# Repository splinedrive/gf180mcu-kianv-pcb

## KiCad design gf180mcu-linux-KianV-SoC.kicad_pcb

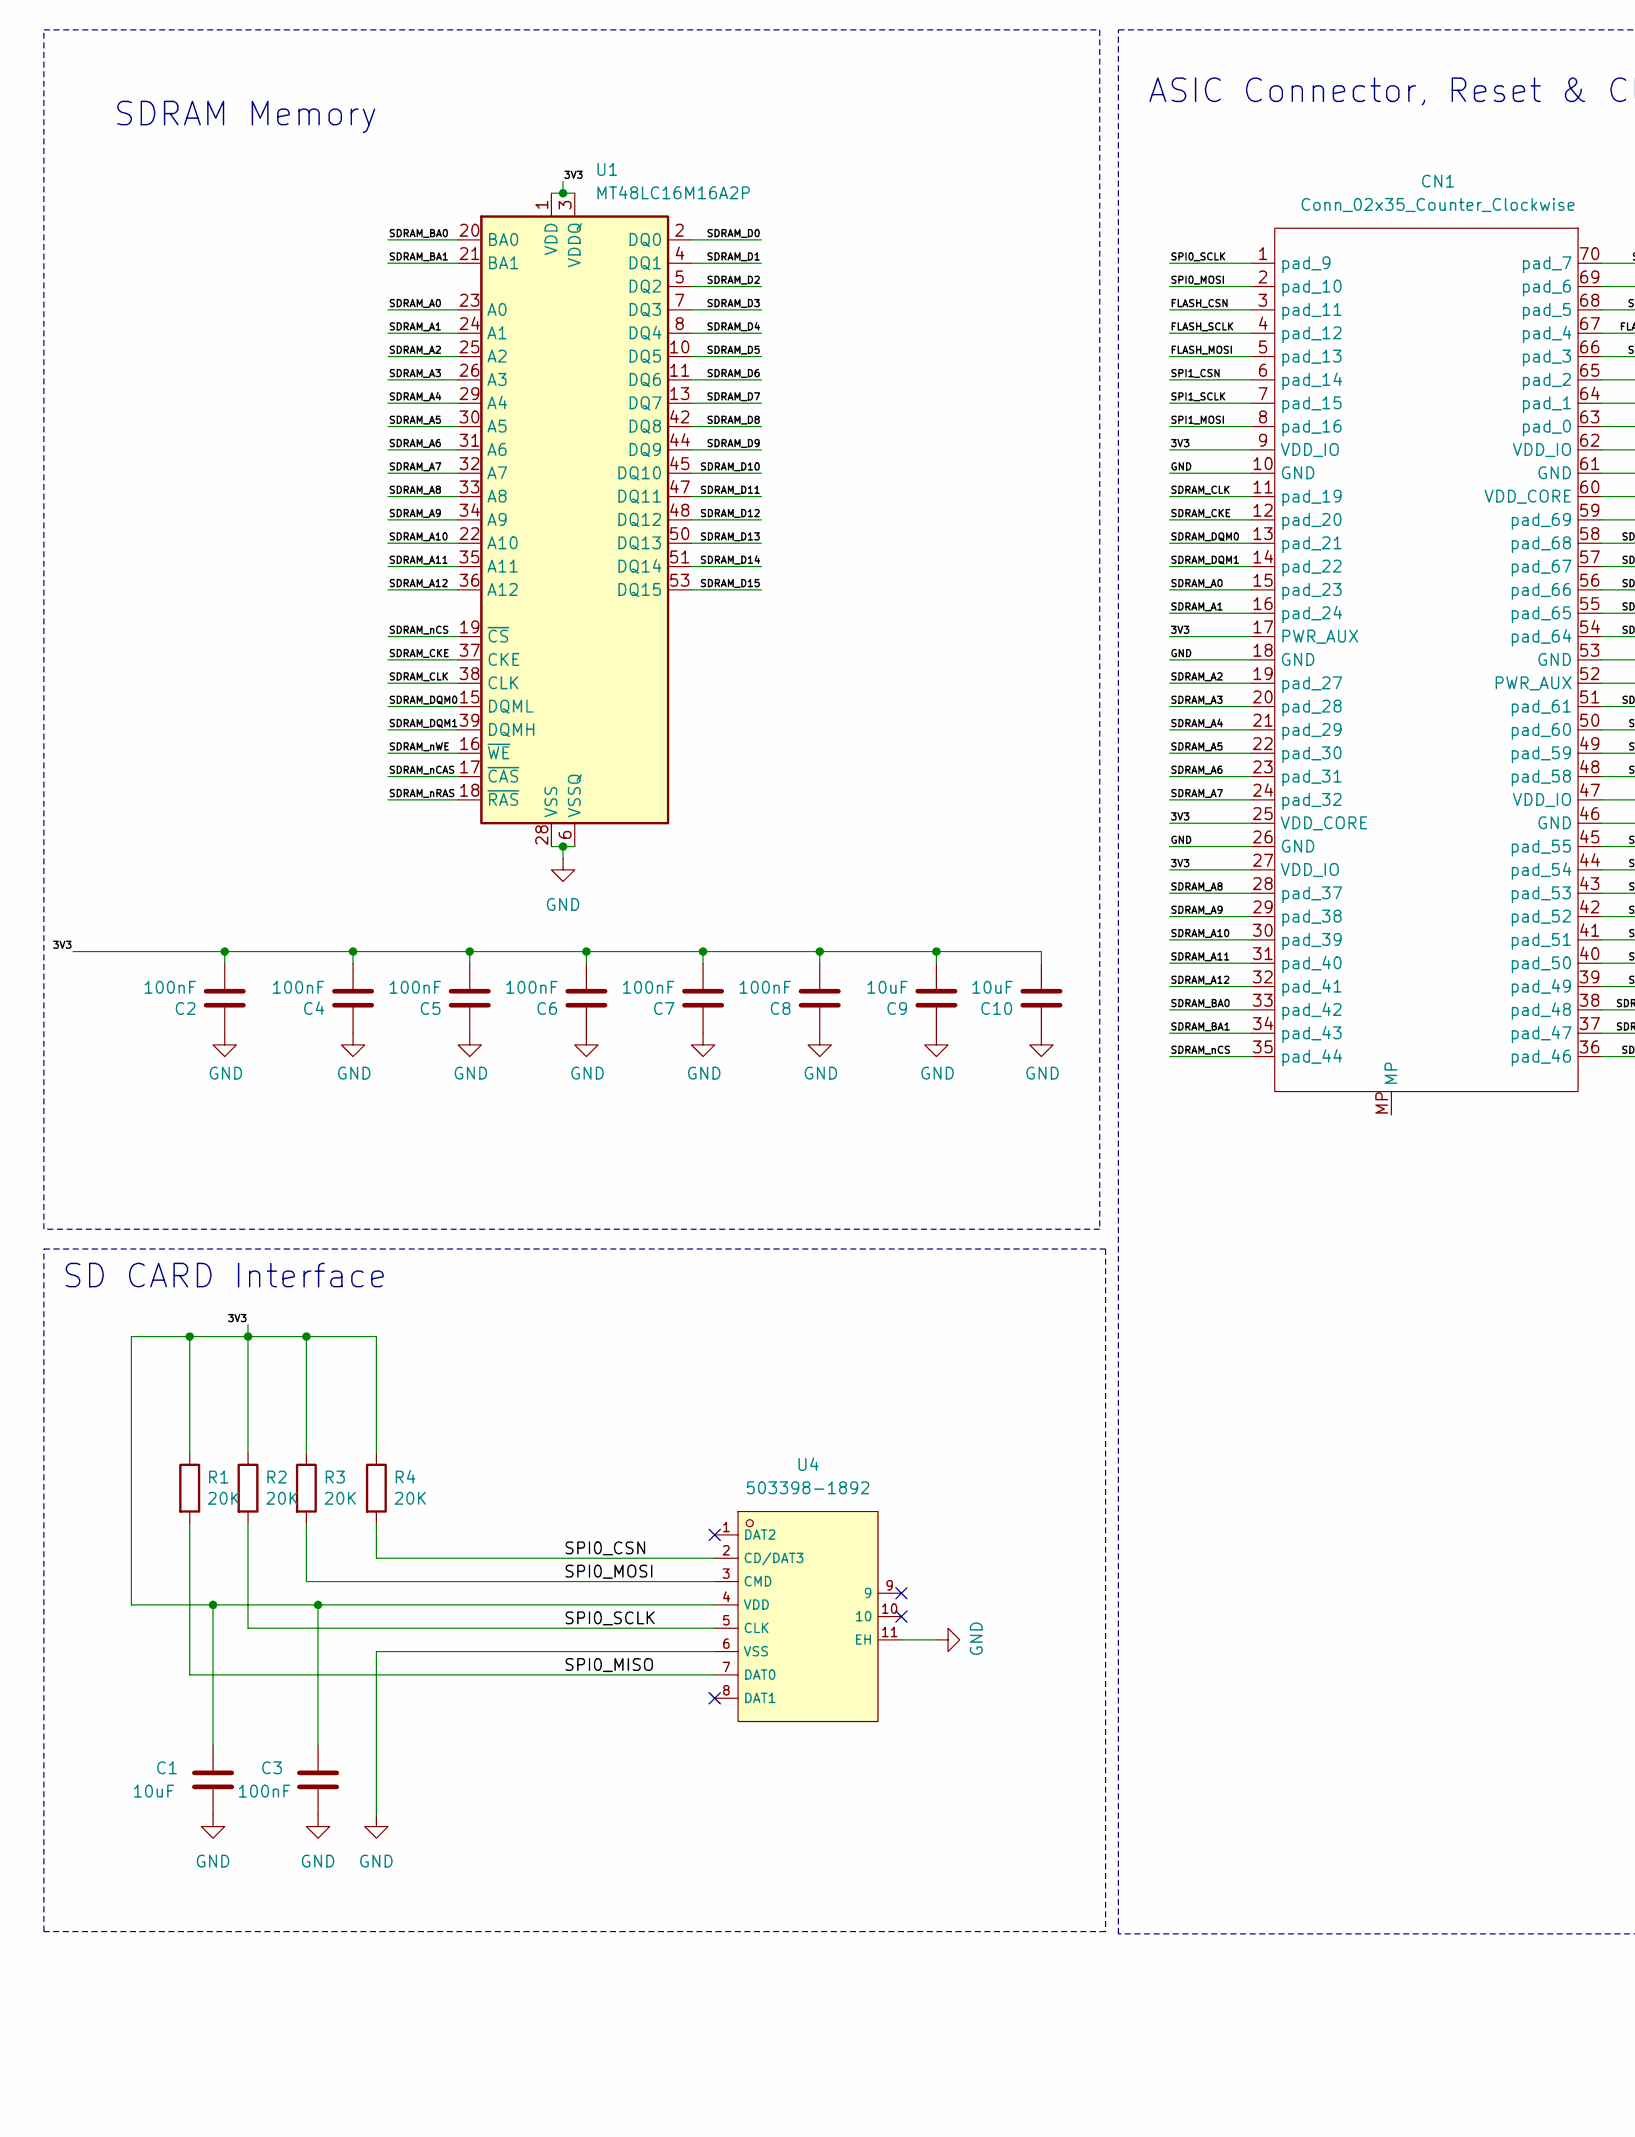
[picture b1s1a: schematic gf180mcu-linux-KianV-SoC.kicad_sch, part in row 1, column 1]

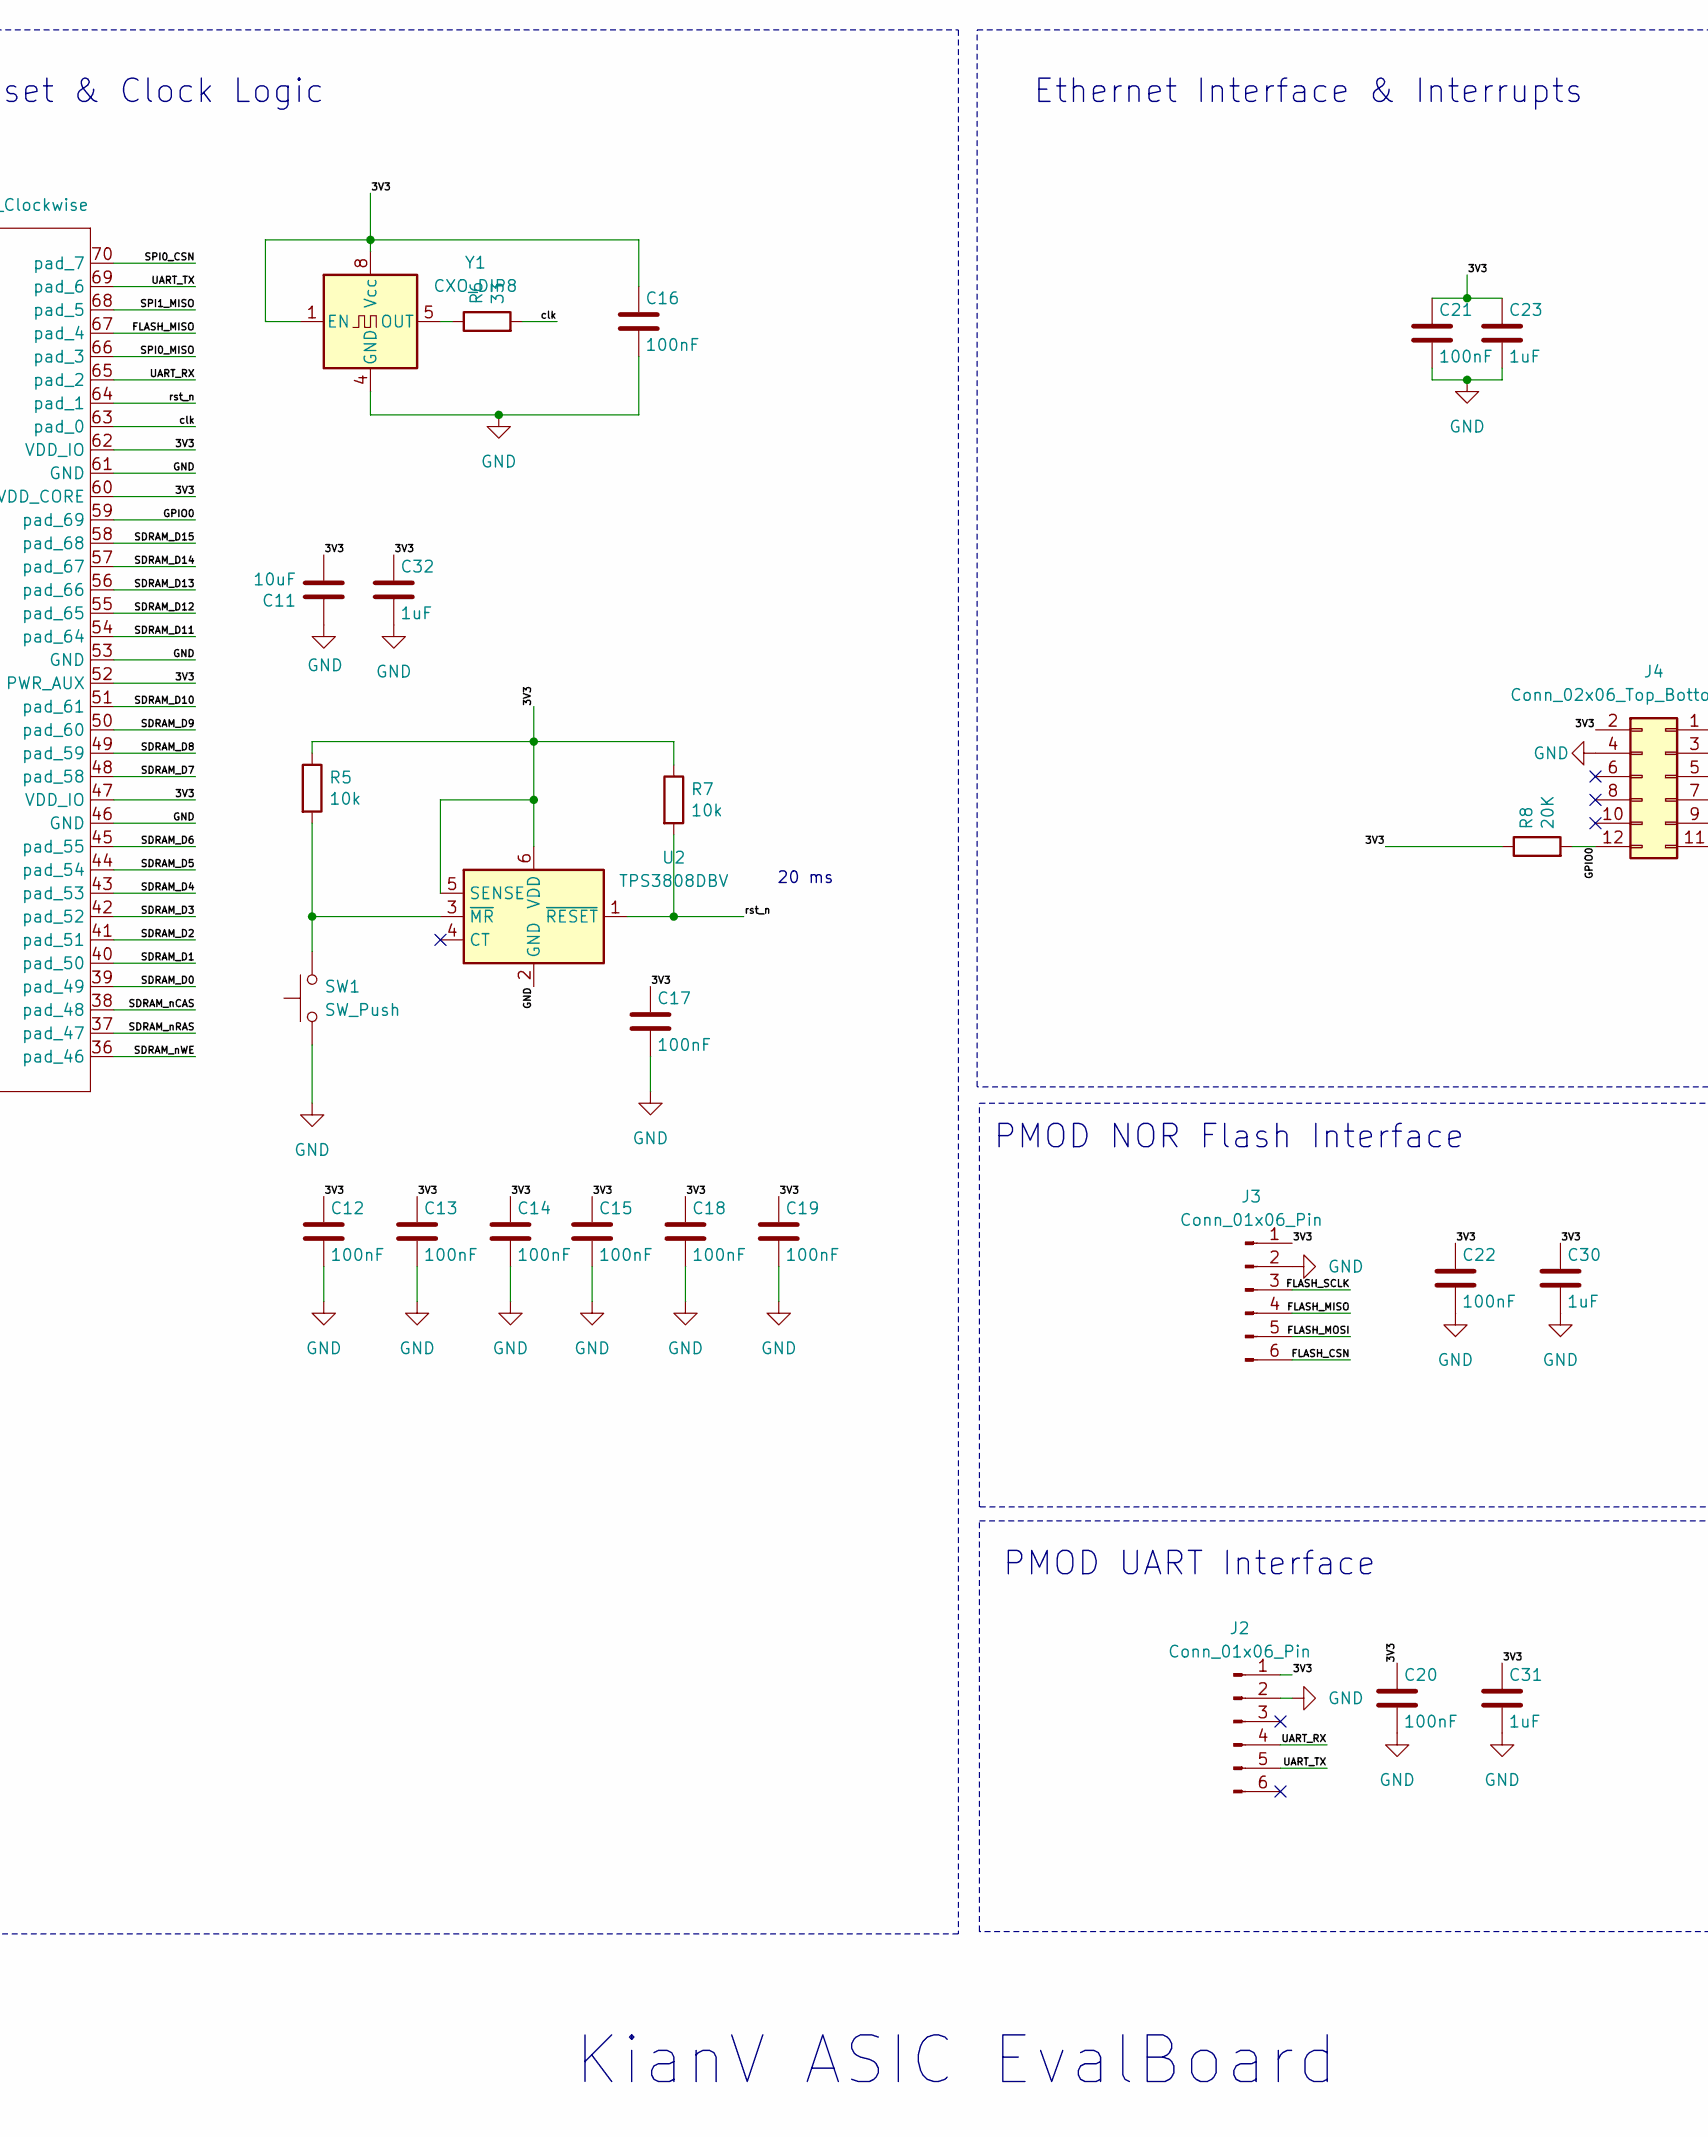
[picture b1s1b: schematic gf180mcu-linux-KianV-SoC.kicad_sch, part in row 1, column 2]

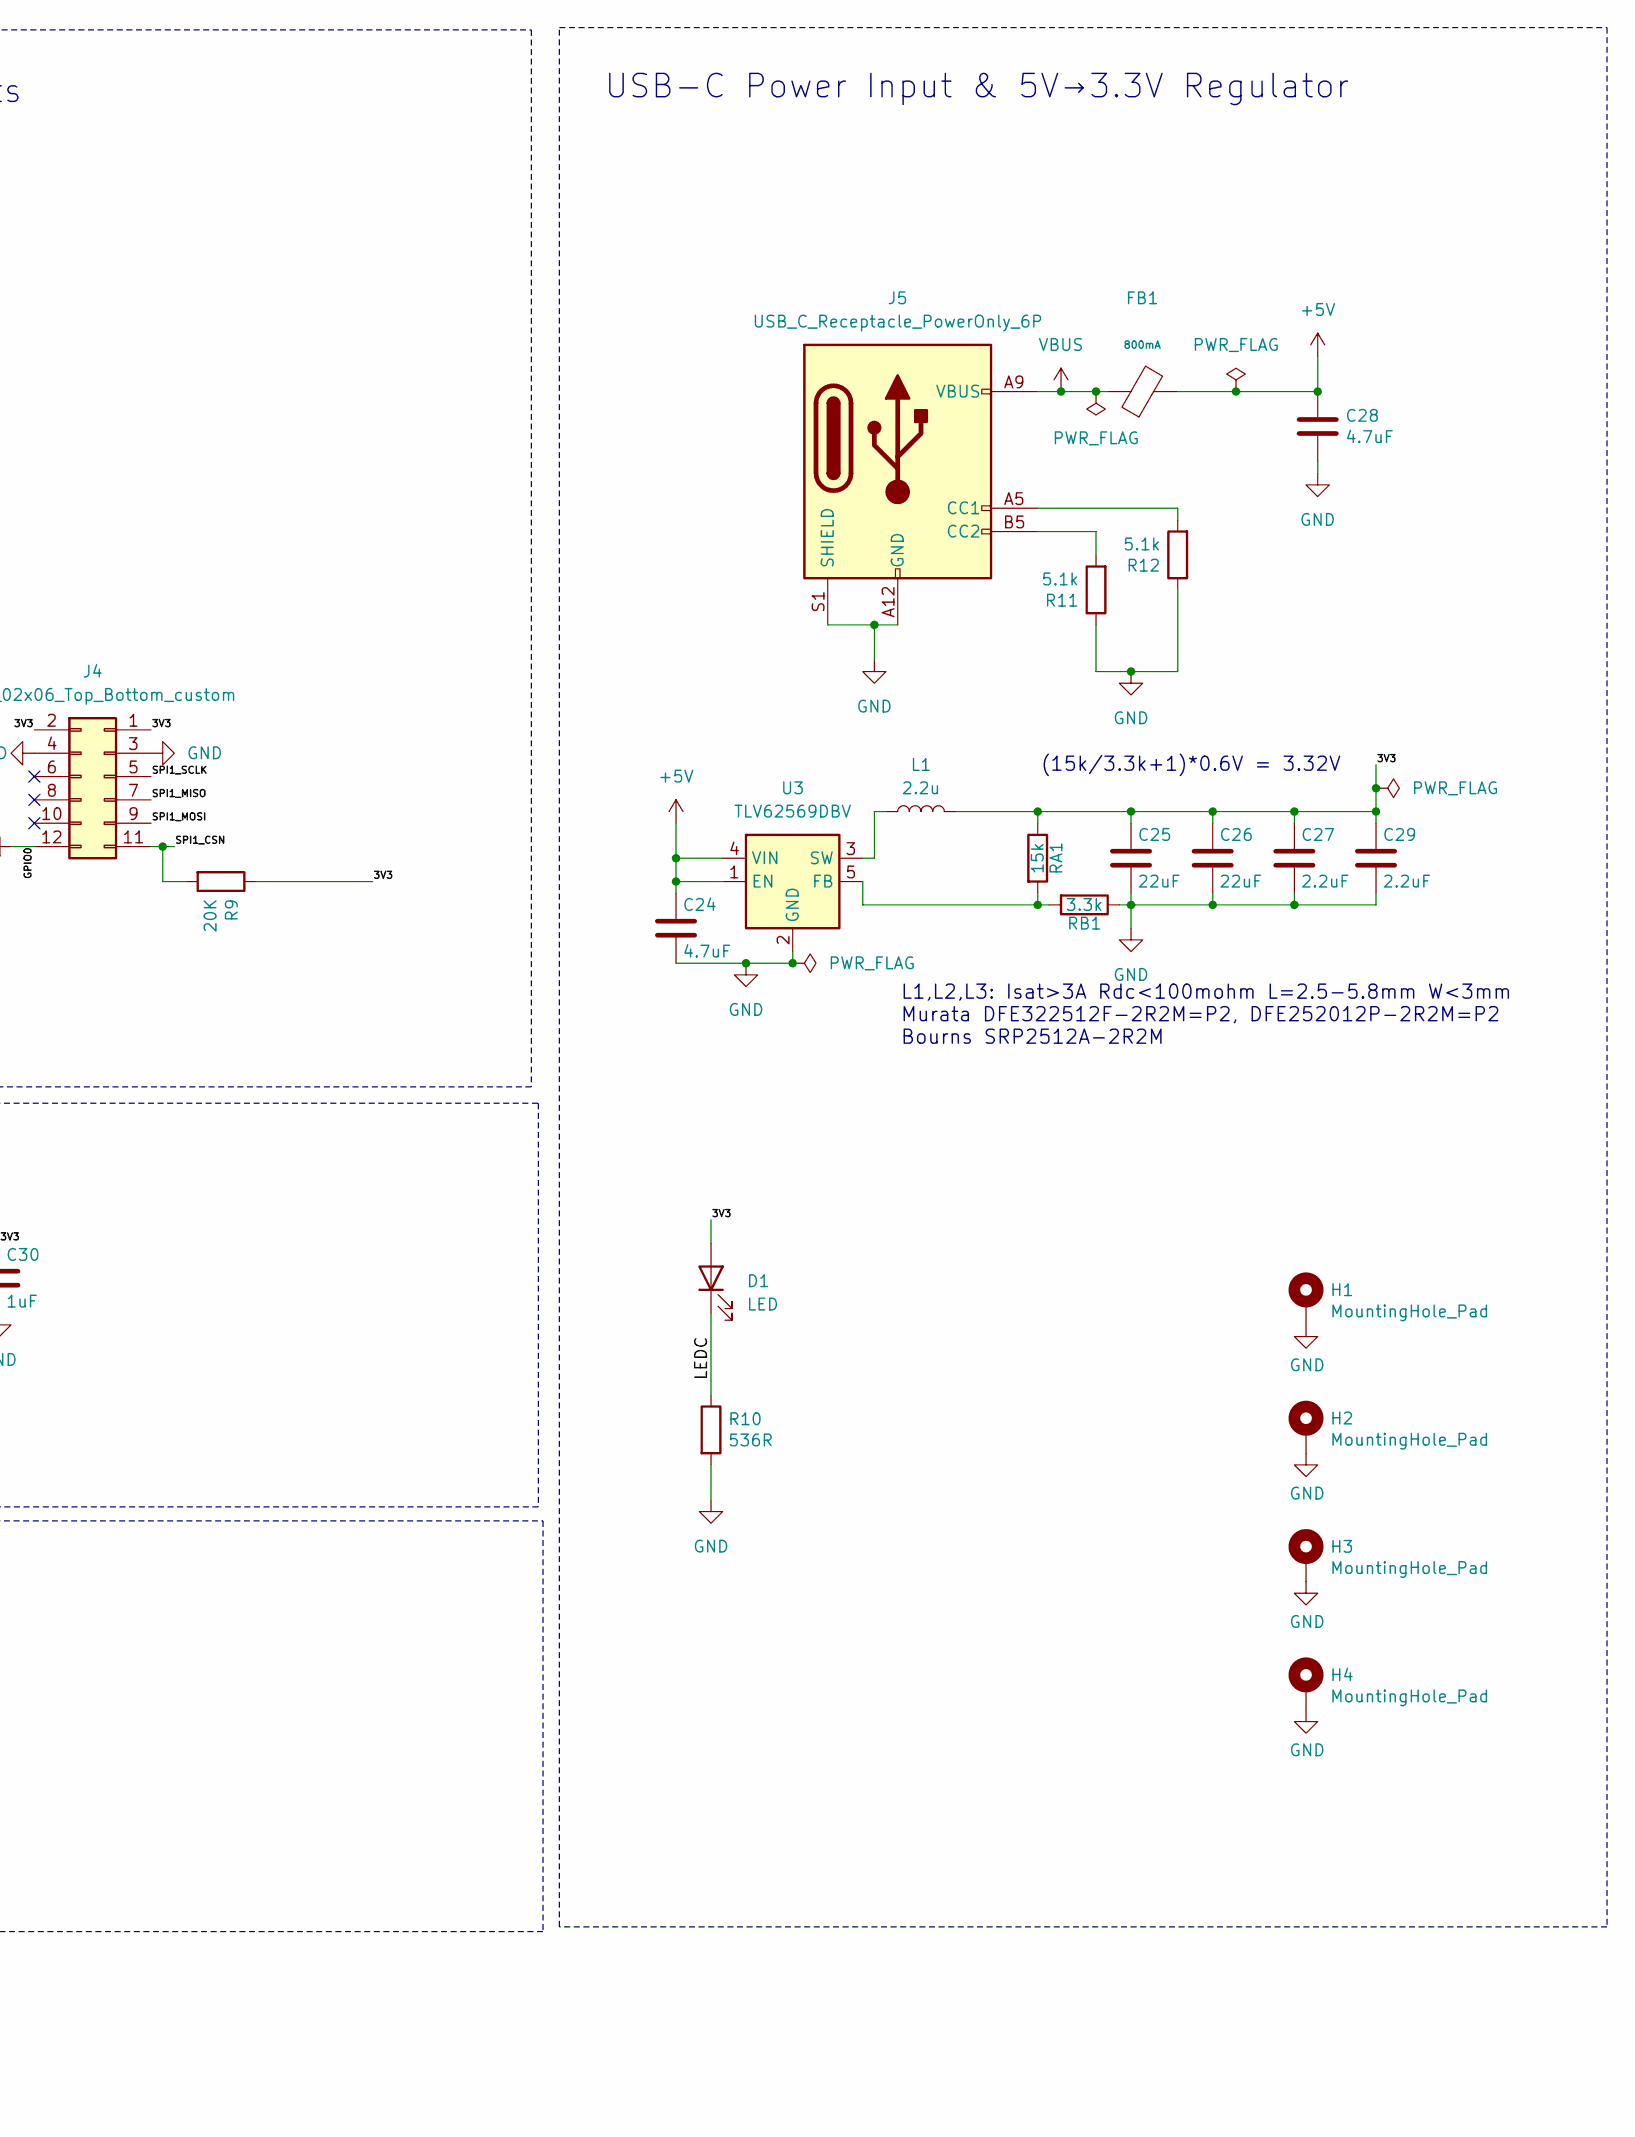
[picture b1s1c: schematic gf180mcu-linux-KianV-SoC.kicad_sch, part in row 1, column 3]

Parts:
C1: 10uF; C_0603
C2, C3, C4, C5, C6, C7, C8: 100nF; C_0603_1608Metric
C9, C10, C11: 10uF; C_0603_1608Metric
C12, C13, C14, C15, C16, C17, C18, C19, C20, C21, C22: 100nF; C_0603_1608Metric; MPN CX0603MRX7R8BB223
C23, C30, C31, C32: 1uF; C_0603_1608Metric; MPN CX0603MRX7R8BB223
C24: 4.7uF; C_0805_2012Metric
C25, C26: 22uF; C_0805_2012Metric
C27, C29: 2.2uF; C_0805_2012Metric
C28: 4.7uF; C_0603_1608Metric
CN1: Conn_02x35_Counter_Clockwise; CONN-SMD_70P-P0.40_HC-PBB40C-70DS-0.4V-3.0-02
D1: LED; LED_0805_2012Metric
FB1: FB_0805; Current Rating 800mA; Tolerance ±25%; Part GZ2012D101TF; LCSC C1015
H1, H2, H3, H4: MountingHole_Pad; MountingHole_3.2mm_M3_Pad
J2, J3: Conn_01x06_Pin; PinSocket_1x06_P2.54mm_Horizontal
J4: Conn_02x06_Top_Bottom_custom; PinSocket_2x06_P2.54mm_Horizontal
J5: USB_C_Receptacle_PowerOnly_6P; USB_C_Receptacle_GCT_USB4125-xx-x-0190_6P_TopMnt_Horizontal
L1: 2.2u; L_0805_2012Metric
R1, R2, R3, R4, R8, R9: 20K; R_0603_1608Metric
R5, R7: 10k; R_0603_1608Metric
R6: 33; R_0603_1608Metric
R10: 536R; R_0603_1608Metric
R11, R12: 5.1k; R_0603_1608Metric
RA1: 15k; R_0603_1608Metric
RB1: 3.3k; R_0603_1608Metric; MPN RT0603FRE073K3L; Mouser 603-RC0603FR-073K3L
SW1: SW_Push; SW_PUSH_6mm_H5mm
U1: MT48LC16M16A2P; TSOP-II-54_22.2x10.16mm_P0.8mm
U2: TPS3808DBV; SOT-23-6
U3: TLV62569DBV; SOT-23-5
U4: 503398-1892; TF-SMD_503398-1892; LCSC C428492
Y1: CXO_DIP8; DIP-8_W7.62mm_Socket

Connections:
+5V: C24.1, C28.1, FB1.2, U3.1 (EN), U3.4 (VIN)
/3V3: C1.1, C2.2, C3.1, C4.2, C5.2, C6.2, C7.2, C8.2, C9.2, C10.2, C11.2, C12.1, C13.1, C14.1, C15.1, C16.1, C17.1, C18.1, C19.1, C20.1, C21.1, C22.1, C23.1, C25.1, C26.1, C27.1, C29.1, C30.1, C31.1, C32.1, CN1.9 (VDD_IO), CN1.17 (PWR_AUX), CN1.25 (VDD_CORE), CN1.27 (VDD_IO), CN1.47 (VDD_IO), CN1.52 (PWR_AUX), CN1.60 (VDD_CORE), CN1.62 (VDD_IO), D1.2 (A), J2.1, J3.1, J4.1, J4.2, L1.2, R1.1, R2.1, R3.1, R4.1, R5.1, R7.1, R8.1, R9.1, RA1.1, U1.1 (VDD), U1.3 (VDDQ), U1.9 (VDDQ), U1.14 (VDD), U1.27 (VDD), U1.43 (VDDQ), U1.49 (VDDQ), U2.5 (SENSE), U2.6 (VDD), U4.4 (VDD), Y1.1 (EN), Y1.8 (Vcc)
/FLASH_CSN: CN1.3 (pad_11), J3.6
/FLASH_MISO: CN1.67 (pad_4), J3.4
/FLASH_MOSI: CN1.5 (pad_13), J3.5
/FLASH_SCLK: CN1.4 (pad_12), J3.3
/GPIO0: CN1.59 (pad_69), J4.12, R8.2
/LEDC: D1.1 (K), R10.1
/SDRAM_A0: CN1.15 (pad_23), U1.23 (A0)
/SDRAM_A1: CN1.16 (pad_24), U1.24 (A1)
/SDRAM_A2: CN1.19 (pad_27), U1.25 (A2)
/SDRAM_A3: CN1.20 (pad_28), U1.26 (A3)
/SDRAM_A4: CN1.21 (pad_29), U1.29 (A4)
/SDRAM_A5: CN1.22 (pad_30), U1.30 (A5)
/SDRAM_A6: CN1.23 (pad_31), U1.31 (A6)
/SDRAM_A7: CN1.24 (pad_32), U1.32 (A7)
/SDRAM_A8: CN1.28 (pad_37), U1.33 (A8)
/SDRAM_A9: CN1.29 (pad_38), U1.34 (A9)
/SDRAM_A10: CN1.30 (pad_39), U1.22 (A10)
/SDRAM_A11: CN1.31 (pad_40), U1.35 (A11)
/SDRAM_A12: CN1.32 (pad_41), U1.36 (A12)
/SDRAM_BA0: CN1.33 (pad_42), U1.20 (BA0)
/SDRAM_BA1: CN1.34 (pad_43), U1.21 (BA1)
/SDRAM_CKE: CN1.12 (pad_20), U1.37 (CKE)
/SDRAM_CLK: CN1.11 (pad_19), U1.38 (CLK)
/SDRAM_D0: CN1.39 (pad_49), U1.2 (DQ0)
/SDRAM_D1: CN1.40 (pad_50), U1.4 (DQ1)
/SDRAM_D2: CN1.41 (pad_51), U1.5 (DQ2)
/SDRAM_D3: CN1.42 (pad_52), U1.7 (DQ3)
/SDRAM_D4: CN1.43 (pad_53), U1.8 (DQ4)
/SDRAM_D5: CN1.44 (pad_54), U1.10 (DQ5)
/SDRAM_D6: CN1.45 (pad_55), U1.11 (DQ6)
/SDRAM_D7: CN1.48 (pad_58), U1.13 (DQ7)
/SDRAM_D8: CN1.49 (pad_59), U1.42 (DQ8)
/SDRAM_D9: CN1.50 (pad_60), U1.44 (DQ9)
/SDRAM_D10: CN1.51 (pad_61), U1.45 (DQ10)
/SDRAM_D11: CN1.54 (pad_64), U1.47 (DQ11)
/SDRAM_D12: CN1.55 (pad_65), U1.48 (DQ12)
/SDRAM_D13: CN1.56 (pad_66), U1.50 (DQ13)
/SDRAM_D14: CN1.57 (pad_67), U1.51 (DQ14)
/SDRAM_D15: CN1.58 (pad_68), U1.53 (DQ15)
/SDRAM_DQM0: CN1.13 (pad_21), U1.15 (DQML)
/SDRAM_DQM1: CN1.14 (pad_22), U1.39 (DQMH)
/SDRAM_nCAS: CN1.38 (pad_48), U1.17 (~CAS)
/SDRAM_nCS: CN1.35 (pad_44), U1.19 (~CS)
/SDRAM_nRAS: CN1.37 (pad_47), U1.18 (~RAS)
/SDRAM_nWE: CN1.36 (pad_46), U1.16 (~WE)
/SPI0_CSN: CN1.70 (pad_7), R4.2, U4.2 (CD/DAT3)
/SPI0_MISO: CN1.66 (pad_3), R1.2, U4.7 (DAT0)
/SPI0_MOSI: CN1.2 (pad_10), R3.2, U4.3 (CMD)
/SPI0_SCLK: CN1.1 (pad_9), R2.2, U4.5 (CLK)
/SPI1_CSN: CN1.6 (pad_14), J4.11, R9.2
/SPI1_MISO: CN1.68 (pad_5), J4.7
/SPI1_MOSI: CN1.8 (pad_16), J4.9
/SPI1_SCLK: CN1.7 (pad_15), J4.5
/UART_RX: CN1.65 (pad_2), J2.4
/UART_TX: CN1.69 (pad_6), J2.5
/clk: CN1.63 (pad_0), R6.2
/rst_n: CN1.64 (pad_1), R7.2, U2.1 (~RESET)
GND: C1.2, C2.1, C3.2, C4.1, C5.1, C6.1, C7.1, C8.1, C9.1, C10.1, C11.1, C12.2, C13.2, C14.2, C15.2, C16.2, C17.2, C18.2, C19.2, C20.2, C21.2, C22.2, C23.2, C24.2, C25.2, C26.2, C27.2, C28.2, C29.2, C30.2, C31.2, C32.2, CN1.10 (GND), CN1.18 (GND), CN1.26 (GND), CN1.46 (GND), CN1.53 (GND), CN1.61 (GND), H1.1 (1_1), H2.1 (1_1), H3.1 (1_1), H4.1 (1_1), J2.2, J3.2, J4.3, J4.4, J5.A12 (GND), J5.B12 (GND), J5.S1 (SHIELD), R10.2, R11.1, R12.1, RB1.1, SW1.1, U1.6 (VSSQ), U1.12 (VSSQ), U1.28 (VSS), U1.41 (VSS), U1.46 (VSSQ), U1.52 (VSSQ), U1.54 (VSS), U2.2 (GND), U3.2 (GND), U4.6 (VSS), U4.11 (EH), Y1.4 (GND)
unnamed: J5.A5 (CC1), R12.2
unnamed: J5.B5 (CC2), R11.2
unnamed: R5.2, SW1.2, U2.3 (~MR)
unnamed: RA1.2, RB1.2, U3.5 (FB)
unnamed: L1.1, U3.3 (SW)
unnamed: R6.1, Y1.5 (OUT)
VBUS: FB1.1, J5.A9 (VBUS), J5.B9 (VBUS)

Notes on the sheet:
(15k/3.3k+1)*0.6V = 3.32V
USB-C Power Input & 5V→3.3V Regulator
20 ms
L1,L2,L3: Isat>3A Rdc<100mohm L=2.5-5.8mm W<3mm Murata DFE322512F-2R2M=P2, DFE252012P-2R2M=P2 Bourns SRP2512A-2R2M
KianV ASIC EvalBoard
PMOD NOR Flash Interface
ASIC Connector, Reset & Clock Logic
Ethernet Interface & Interrupts
PMOD UART Interface
SD CARD Interface
SDRAM Memory

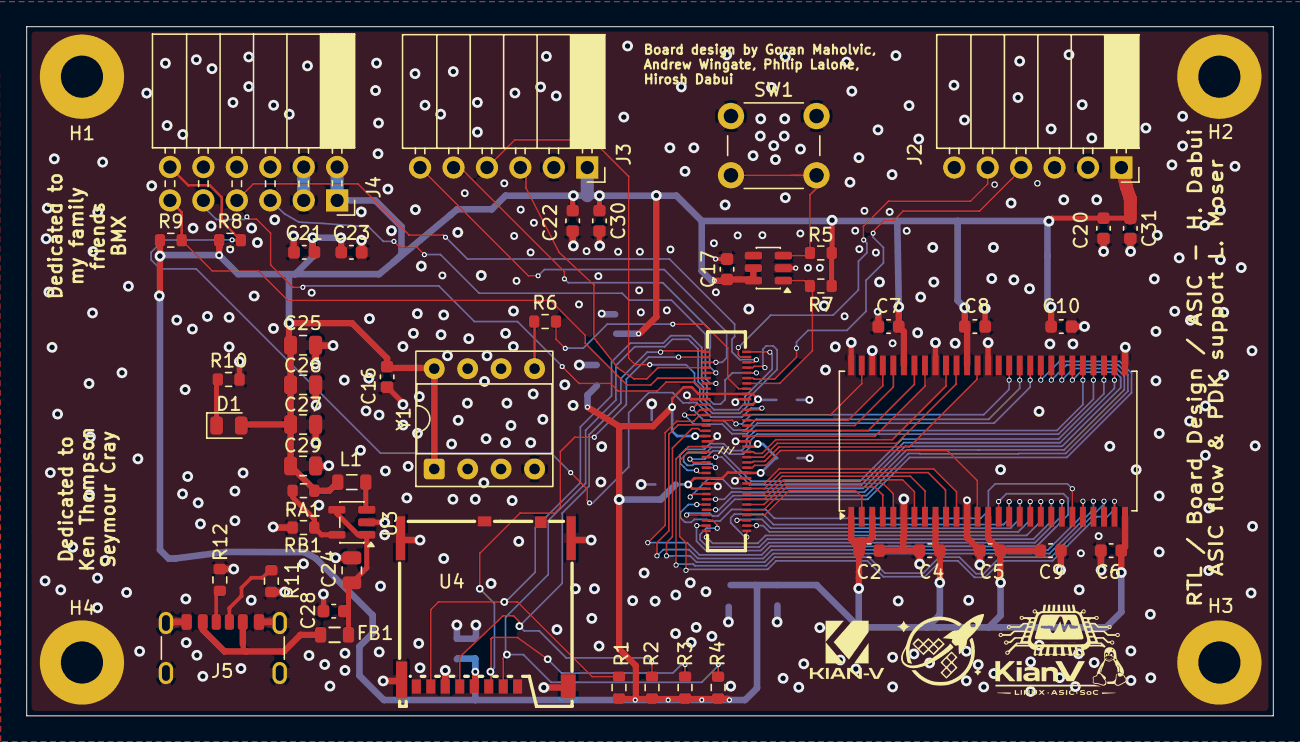
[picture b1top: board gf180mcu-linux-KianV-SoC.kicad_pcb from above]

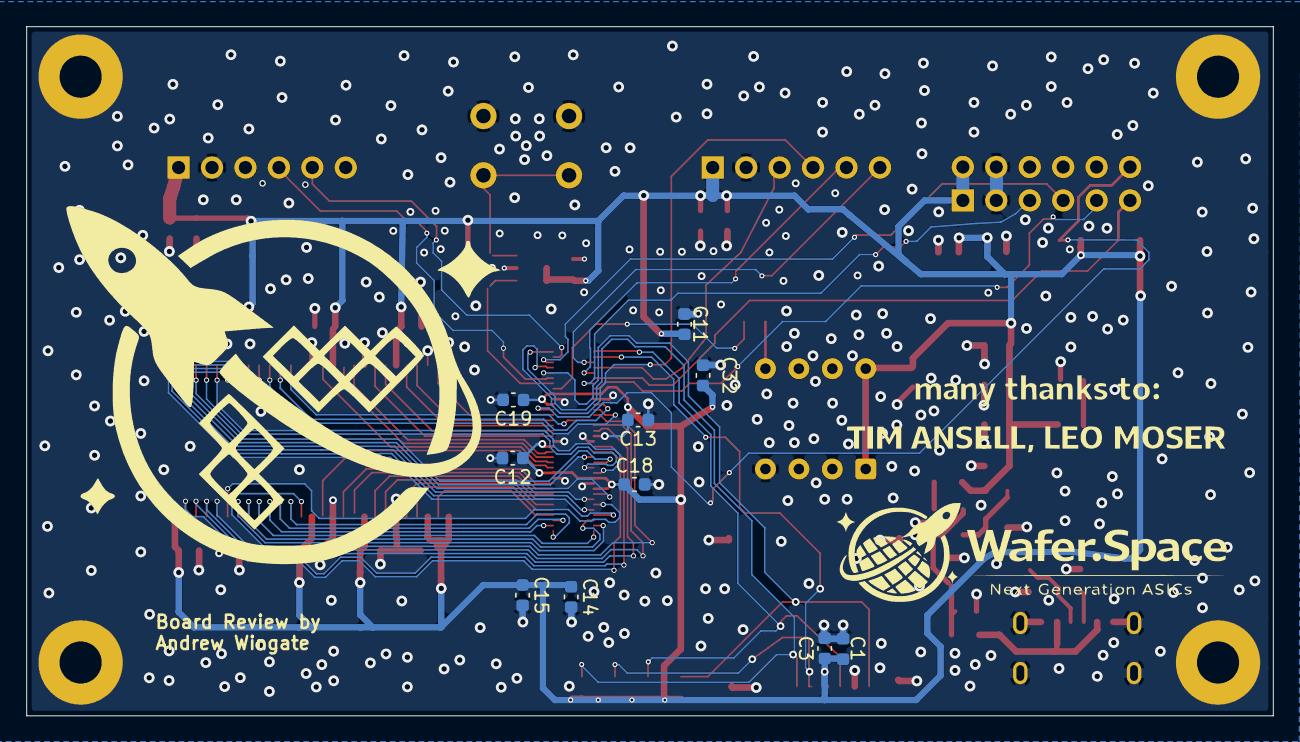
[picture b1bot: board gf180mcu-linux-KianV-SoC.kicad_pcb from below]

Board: 4 copper layers, 94.7 x 52.4 mm, 64 parts (10 on the bottom side), 67 nets.

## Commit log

2026-01-10 Add KiCad project (gf180mcu-linux-KianV-SoC)
2026-01-11 fixed sdcard
2026-01-11 rework: silk
2026-01-14 small tweaks
2026-01-15 first pass complete
2026-01-15 rework: silk text, sdram cap gnd, power lines, ...
2026-01-16 more comments
2026-01-20 kicad: fix capacitor footprints + add GND stitching vias
    Switch C1/C3/C28 from resistor footprints to proper 0603 capacitor footprints (C1 to JLCPCB lib + 3D model)
    Tweak pad sizes/placement + silkscreen/ref visibility
    Add additional GND vias for stitching and minor route/via coordinate cleanup
2026-01-21 andrew's small tweaks
2026-02-03 pcb: DFM cleanup, SD card footprint update, oscillator fixes
2026-06-10 update connector assigments and reroute
2026-06-10 remove drc warnings, added machdyne credit
2026-06-11 rounded vcc signal
2026-06-17 Set C24 to 4.7uF
